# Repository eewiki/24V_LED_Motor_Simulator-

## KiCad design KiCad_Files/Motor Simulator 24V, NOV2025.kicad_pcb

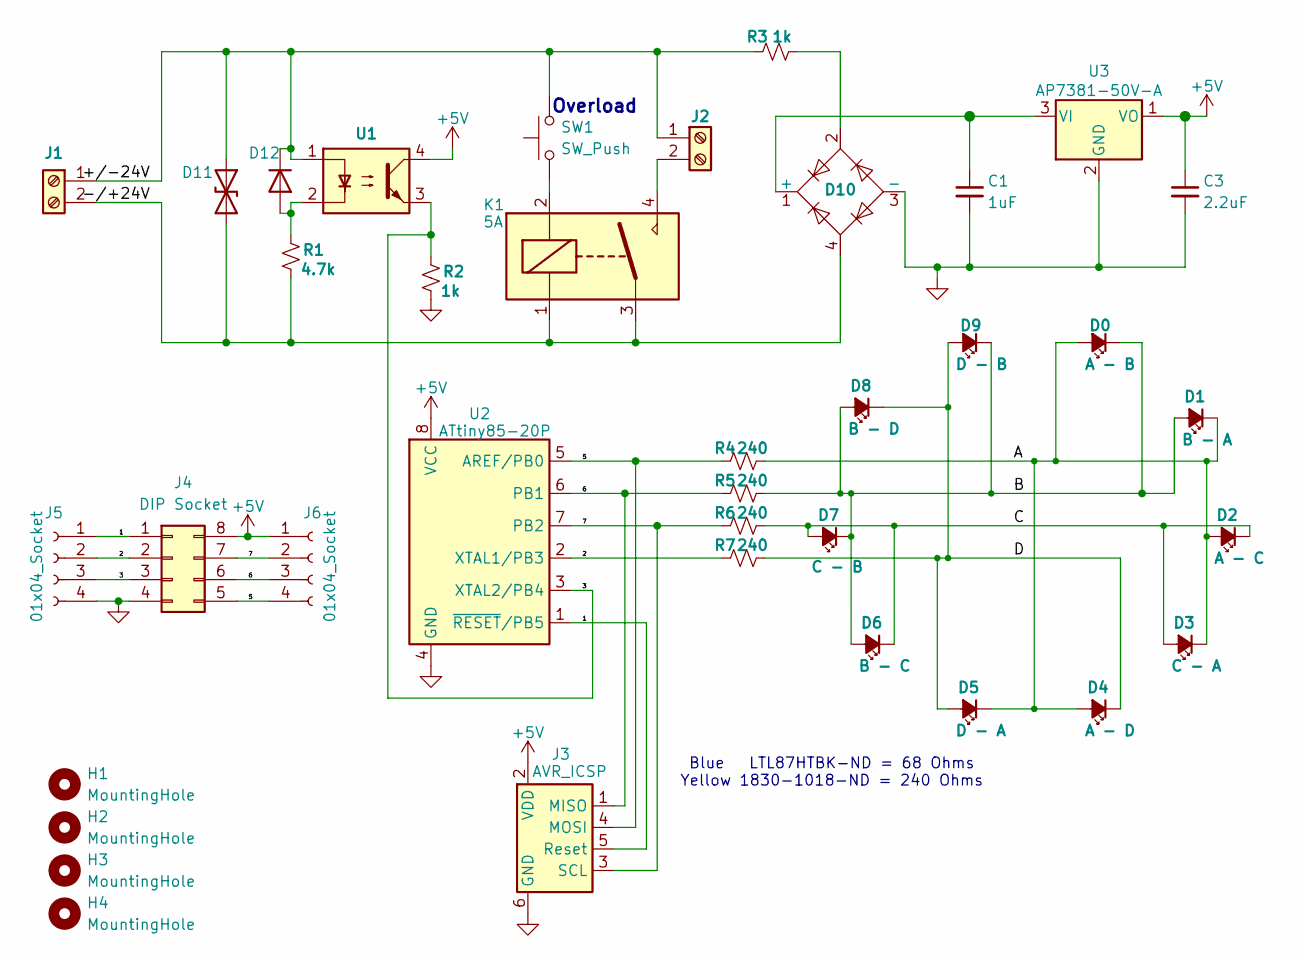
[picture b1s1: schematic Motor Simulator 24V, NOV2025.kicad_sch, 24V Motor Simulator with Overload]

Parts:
C1: 1uF; C_Disc_D3.0mm_W1.6mm_P2.50mm
C3: 2.2uF; C_Disc_D3.0mm_W1.6mm_P2.50mm
D0: A - B; LED_D3.0mm
D1: B - A; LED_D3.0mm
D2: A - C; LED_D3.0mm
D3: C - A; LED_D3.0mm
D4: A - D; LED_D3.0mm
D5: D - A; LED_D3.0mm
D6: B - C; LED_D3.0mm
D7: C - B; LED_D3.0mm
D8: B - D; LED_D3.0mm
D9: D - B; LED_D3.0mm
D10: B80R; Diode_Bridge_Round_D9.0mm
D11: D_TVS; D_DO-41_SOD81_P7.62mm_Horizontal
D12: 1N4148; D_DO-35_SOD27_P7.62mm_Horizontal
H1, H2, H3, H4: MountingHole; MountingHole_4.4mm_#8
J1, J2: Screw_Terminal_01x02; TermBlock_Lever_1818-QT02ASB83H0000G-ND
J3: AVR_ICSP; PinHeader_2x03_P2.54mm_Vertical
J4: DIP Socket
J5: 01x04_Socket; PinSocket_1x04_P2.54mm_Vertical_Staggered_Left
J6: 01x04_Socket; PinSocket_1x04_P2.54mm_Vertical_Staggered_Right
K1: 5A; Relay_J113__SPST
R1: 4.7k; R_Axial_DIN0204_L3.6mm_D1.6mm_P5.08mm_Horizontal
R2, R3: 1k; R_Axial_DIN0204_L3.6mm_D1.6mm_P5.08mm_Horizontal
R4, R5, R6, R7: 240; R_Axial_DIN0204_L3.6mm_D1.6mm_P5.08mm_Horizontal
SW1: SW_Push; SW_NCA2
U1: Optocoupler_DC_PhotoNPN_AKEC; DIP-4_W7.62mm_LongPads
U2: ATtiny85-20P; DIP-8_W7.62mm
U3: AP7381-50V-A; TO-92_HandSolder

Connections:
+5V: C3.1, J3.2 (VDD), J4.8, J6.1, U1.4, U2.8 (VCC), U3.1 (VO)
/1: J3.5 (Reset), J4.1, J5.1, U2.1 (~RESET/PB5)
/2: J4.2, J5.2, R7.1, U2.2 (XTAL1/PB3)
/3: J4.3, J5.3, R2.1, U1.3, U2.3 (XTAL2/PB4)
/5: J3.4 (MOSI), J4.5, J6.4, R4.1, U2.5 (AREF/PB0)
/6: J3.1 (MISO), J4.6, J6.3, R5.1, U2.6 (PB1)
/7: J3.3 (SCL), J4.7, J6.2, R6.1, U2.7 (PB2)
/22.6V_(24V_-_0.7V_x_2): C1.1, D10.1 (+), U3.3 (VI)
/+/-24V: D11.1 (A1), D12.1 (K), J1.1, J2.1, R3.1, SW1.2, U1.1
/-/+24V: D10.4, D11.2 (A2), J1.2, K1.1, K1.3, R1.2
GND: C1.2, C3.2, D10.3 (-), J3.6 (GND), J4.4, J5.4, R2.2, U2.4 (GND), U3.2 (GND)
unnamed: D0.2 (A), D1.1 (K), D2.2 (A), D3.1 (K), D4.2 (A), D5.1 (K), R4.2
unnamed: D0.1 (K), D1.2 (A), D6.2 (A), D7.1 (K), D8.2 (A), D9.1 (K), R5.2
unnamed: D2.1 (K), D3.2 (A), D6.1 (K), D7.2 (A), R6.2
unnamed: D4.1 (K), D5.2 (A), D8.1 (K), D9.2 (A), R7.2
unnamed: D10.2, R3.2
unnamed: D12.2 (A), R1.1, U1.2
unnamed: J2.2, K1.4
unnamed: K1.2, SW1.1

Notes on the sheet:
Blue LTL87HTBK-ND = 68 Ohms Yellow 1830-1018-ND = 240 Ohms
Overload

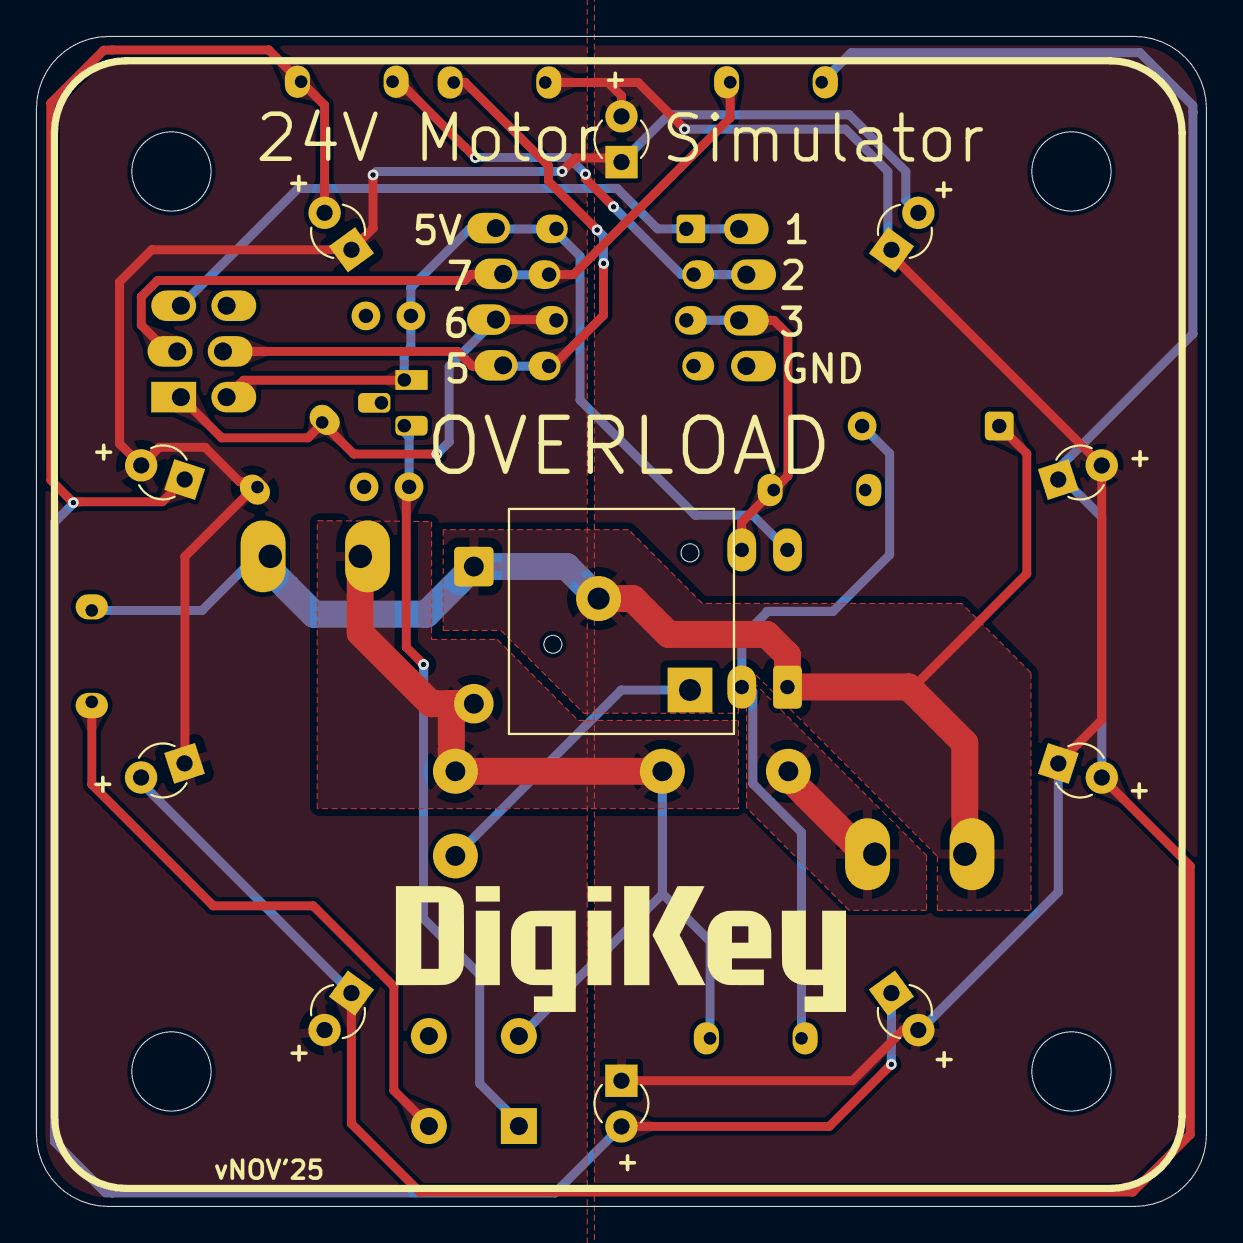
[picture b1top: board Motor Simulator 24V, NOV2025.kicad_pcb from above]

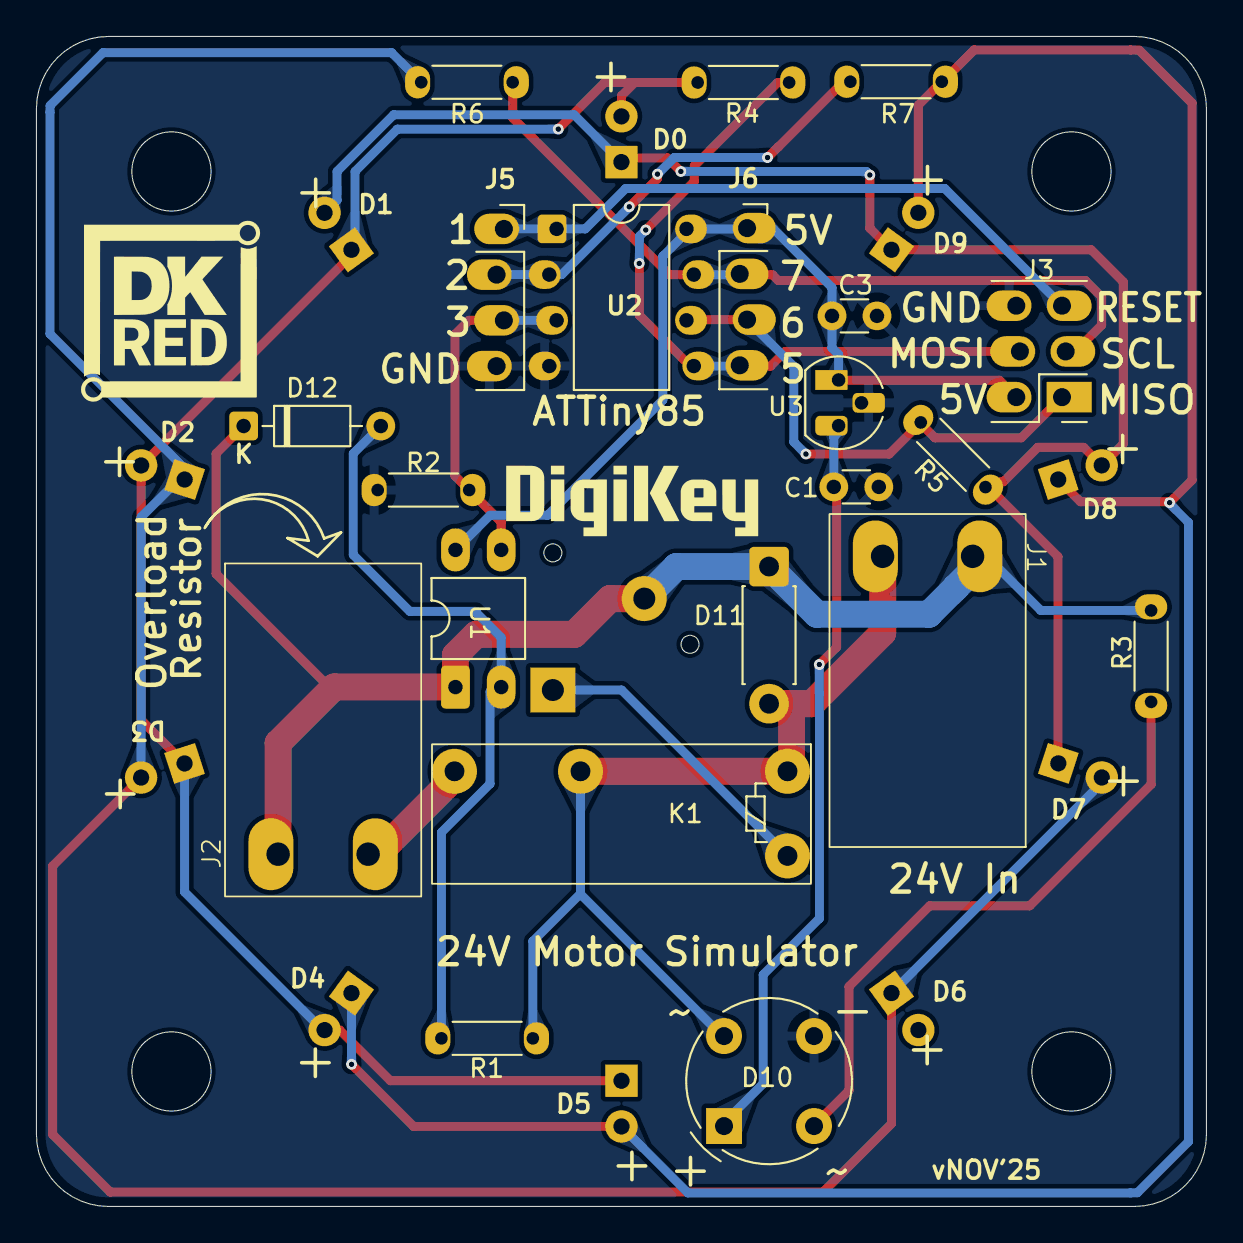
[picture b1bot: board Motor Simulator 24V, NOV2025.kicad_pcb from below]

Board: 2 copper layers, 65.0 x 65.0 mm, 37 parts (21 on the bottom side), 19 nets.

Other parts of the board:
G1: LOGO

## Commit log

2026-03-25 Rename Motor Simulator 24V, NOV2025.zip to Motor_Simulator_24V,_NOV2025,_KiCad_Files.zip
